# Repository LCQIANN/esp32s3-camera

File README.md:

# ESP32-S3 Camera — v1.4

以 ESP32-S3-WROOM-1-N16R8 為核心的隨身相機板：OV2640 DVP 相機、microSD 存檔、USB-C 燒錄與充電、鋰電池供電、電源開關與電源燈，1.3 吋 ST7789 預覽螢幕直接插在背面的母座上，快門在上板邊側按。v1.3 起為 3D 列印相機式外殼（鏡頭正面、螢幕背面）而改，v1.4 把快門移到上板邊。KiCad 10 專案，設計成直接送 JLCPCB PCBA。

| 項目 | 規格 |
|---|---|
| 板子 | 60 × 85 mm、4 層（In1 = GND、In2 = +3V3）、1.6 mm、四角 M2 孔 |
| 主控 | U1 ESP32-S3-WROOM-1-N16R8（16 MB flash、8 MB OPI PSRAM） |
| 相機 | J2 24P 0.5 mm FPC 座，AI-Thinker ESP32-CAM 標準腳位；U5 2.8V、U6 1.2V LDO 供相機 |
| 儲存 | J3 microSD（SDMMC），開口朝左板邊 |
| 電源 | J1 USB-C → U3 TP4056 充電 → J4 JST PH 2.0 鋰電池；U2 AP2112K 3.3V LDO；SW4 滑動開關控制 LDO EN；D5 藍色電源燈 |
| 操作 | SW3 SHUTTER 側按式（ALPS SKRTLAE010）在上板邊右段 (50.6, 2.6)；SW1 BOOT、SW2 RESET 頂面按壓式在左欄；D1 綠、D2 紅（充電）、D4 白 LED |
| 螢幕 | J5 1×7 2.54 mm 母座（底面右板邊），通用型 1.3 吋 IPS 240×240 ST7789 7 pin 模組，用七條公–母杜邦線接（2026-09-23 起；也可直插）；SCL=GPIO44、SDA=GPIO43、RES=GPIO6、DC=GPIO5、BLK=GPIO4。UART0 排針已取消 |
| 零件 | 60 顆：58 SMD 由 JLCPCB 貼片，2 插件（J4 電池座、J5 螢幕母座） |
| 狀態 | v1.4，2026-09-22 定稿。ERC 0、DRC 0/0/0、原理圖一致性 0、GND/3V3 連通性 0 孤立焊盤 |

## 目前狀態

- **v1.4 已定稿，可下單。** 快照在 `versions/v1.4/`，含 Gerber、BOM、CPL、ERC/DRC 報告，視為唯讀。v1.2、v1.3 都沒有下單。
- **預覽螢幕用七條公–母杜邦線接板上母座 J5**（2026-09-23 決定，省事不焊；腳序一對一）。模組鎖在後殼四支矮柱上、蓋在電池上方，亮面離板底約 26.4 mm；外殼後半因為杜邦膠殼加深到 27 mm 內深，整機 40.1 mm。細節與外殼用的尺寸在 `DESIGN.md` 2d 節與 `enclosure/README.md`。
- 版本沿革：v1.0 最初佈局 → v1.1 相機腳位改 ESP32-CAM 標準、加相機 LDO、填 LCSC 料號 → v1.2 加 SW4、R21、R20、D5 與 ON/OFF 絲印 → v1.3 J5/J6 兩條排針換成 1×7 螢幕母座 J5（SMD 與 CPL 不變）→ v1.4 快門 SW3 換成側按式移到上板邊右段，C12 下移 0.8 mm（CPL 只差這兩行）。
- 外殼相關但仍刻意沒改：LED 分兩面、板邊開口分三邊（USB-C 與開關右邊、記憶卡左邊、快門上邊）。
- 送洗前檢查補了兩顆 GND 過孔（J2.23、C3.2 原本焊盤浮接），細節見 `DESIGN.md` 第 3 節。

## 簡報

| 檔案 | 給誰看 | 內容 |
|---|---|---|
| `esp32s3-camera-v1.4-簡易版.pptx` / `.pdf` | 外行人、家人朋友、沒碰過電路板的人 | 11 頁，不用零件編號與專業縮寫：它能做什麼、正反面長什麼樣、工廠做哪些我們做哪些、要買什麼、三步組裝、三件注意事項、外殼長這樣、裝進殼裡長這樣 |
| `esp32s3-camera-v1.4.pptx` / `.pdf` | 自己下單與組裝時對照、有電子背景的人 | 21 頁完整版：依 PCB 座標畫的零件分工圖、Economic / Standard 差異、58 顆 SMD 清單、3D 渲染、組裝尺寸與高度、四頁 3D 列印外殼（含板外零件裝配檢查與杜邦線走線）、含購買連結的採購表；2026-09-23 已更新為杜邦線版 |

另有一個線上頁面「ESP32-S3 相機板零件分工圖」（claude.ai 私人連結，組織內可看），2026-09-23 已更新到 v1.4 杜邦線版：依座標畫的零件分工圖、組裝示意與裸板 3D 渲染、外殼與杜邦線走線渲染、採購清單。

兩份都用 PowerPoint 匯出成 PDF，PDF 內的購買連結可點。兩份簡報 2026-09-23 已更新到 v1.4（螢幕母座、側按快門、外殼）；更新方式是 `tools/update_decks_v14.py` 在 v1.2 檔上改文字、換圖、加頁，再用 `tools/export_decks.py` 叫 PowerPoint 匯出 PDF 與檢查用的 PNG。

## 檔案地圖

```
esp32s3-camera/
├── README.md                     本檔
├── DESIGN.md                     設計規格書：決策、腳位、電路細節、組裝與機構、版本規則
├── esp32s3-camera.kicad_pro/.kicad_sch/.kicad_pcb   KiCad 10 專案（根目錄永遠是最新版）
├── esp32s3-camera.pretty/        自訂 footprint（ESP32-S3-WROOM-1-Cam）
├── esp32s3-camera.step           板子 STEP，給外殼設計用
├── erc.rpt / drc.rpt / netlist.net
├── view-top.png / view-bottom.png   v1.4 頂面、底面 3D 正視
├── esp32s3-camera-v1.4.pptx / .pdf   零件分工、組裝示意、渲染圖、外殼、採購清單簡報（完整版 20 頁）
├── esp32s3-camera-v1.4-簡易版.pptx / .pdf   給外行人看的 11 頁簡易版
├── tools/                        簡報更新與匯出腳本（python-pptx + PowerPoint COM）
│
├── fab/                          送廠檔案
│   ├── esp32s3-camera-gerber.zip   Gerber + 鑽孔打包
│   ├── esp32s3-camera-bom.csv      BOM，含 LCSC Part # 欄
│   ├── esp32s3-camera-cpl.csv      貼片座標
│   ├── gerber/                     未打包的 Gerber、鑽孔檔
│   ├── JLCPCB-上傳-v1.4/            上傳用三個檔案的重新命名版 + 一頁說明
│   ├── JLCPCB-下單清單.md           下單逐步核對表，含收到板子後的第一次上電
│   └── 採購清單.md                  板外零件與插件的購買網址
│
├── render/                       kicad-cli 光線追蹤渲染
│   ├── iso-*/top/bottom/low-angle/closeup-*.png   裸板貼片後
│   ├── assembled-*.png / closeup-camera-module.png   插相機、記憶卡、電池、螢幕的組裝示意
│   └── illustration/             示意渲染專用的板檔複本、簡化 VRML 模型、輔助腳本（見下）
│
├── versions/                     各版完整快照，唯讀
│   ├── v1.0/  v1.1/  v1.2/  v1.3/  v1.4/   每版有 README.txt 說明改了什麼
│
├── enclosure/                    3D 列印外殼：SolidWorks 前殼、後殼、按鈕帽、組合件、STL、渲染圖與產生腳本（見 enclosure/README.md）
├── firmware/                     Arduino 韌體：預覽、拍照存卡、閃光燈（見 firmware/README.md）
├── frames/                       2026-09-11 早期佈局的旋轉截圖，僅供回顧
└── .history/                     KiCad 自動快照，由 KiCad 管理
```

`render/illustration/esp32s3-camera-illustration.kicad_pcb` 多了三個沒有焊盤的假零件掛簡化模型，**只用來渲染，不要拿它出 Gerber**。

## 怎麼下單

1. 依 `fab/JLCPCB-下單清單.md` 逐項核對。上傳 `fab/esp32s3-camera-gerber.zip`、`esp32s3-camera-bom.csv`、`esp32s3-camera-cpl.csv`。
2. PCB：4 層、60 × 85 mm、1.6 mm、1 oz、ENIG 建議、Tented via，最少 5 片。
3. PCBA：雙面貼片，最少 2 片。
   - **Economic** 只焊 SMD：J4 電池座、J5 1×7 母座（C225482）自己買回來手焊。
   - **Standard** 含插件：兩顆一起焊好。
4. 料號配對頁逐行看：U1 `C2913202`（N16R8，可能預購，不要被換成 N8 或無 R 版）、D3 `C8598`（SOD-123，不是 SS14）、SW4 `C431540`、SW3 `C110293`（ALPS SKRTLAE010 側按，不要被換成頂按式）。
5. 零件擺放預覽確認方向：U1 天線端朝板子底邊、J1 開口朝板邊、J2 掀蓋朝板邊、SW4 撥桿朝右板邊、**SW3 觸桿朝上板邊**、J5 母座在底面、方形 pin 1 焊盤朝天線那一端。

## 板外要自己買的

相機模組、鋰電池、microSD 卡、USB-C 線是最小採購；Economic 方案再加 J4 電池座。完整清單與購買網址在 `fab/採購清單.md`。

| 品項 | 規格 | 接到 |
|---|---|---|
| OV2640 相機模組 | 24 pin 0.5 mm 排線，ESP32-CAM 相容，排線約 21 mm，多買一條備用 | J2 |
| 3.7V 鋰電池 | 603040 或 503040 約 600 mAh，帶保護板，JST PH 2.0 插頭 | J4 |
| microSD 卡 | 8–32 GB | J3 |
| USB-C 線 | 要能傳資料 | J1 |
| 預覽螢幕 | 通用型 1.3 吋 IPS 240×240 ST7789，7 pin 2.54 mm 直排針已焊，27.78 × 39.22 mm | 七條公–母杜邦線接 J5 |
| 杜邦線 | 公–母、10 cm、7 條 | 公頭插 J5、母頭套螢幕排針 |
| M2 螺絲與銅柱 | 板子 4 組 | H1–H4 |
| 雙面泡棉膠 | 約 2 mm 厚 | 相機模組與電池底下 |

## 組裝重點

- **相機**：排線接觸面朝下插入 J2，出來約 2.5 mm 就反折 180° 蓋回 J2，模組貼在按鍵欄與 U4 之間的空區（x 25.5–34.5、y 20.5–29.5 mm），鏡頭中心 (30, 25)，底下墊 8 × 8 mm 泡棉膠。
- **電池**：貼在底面中央 (34, 44)，墊 2 mm 泡棉，保護板端朝下緣。**J4 pin 1 = 正極**，在 L 形絲印那一側、靠板子中央。電池插頭極性沒有統一規範，插之前先量。
- **螢幕**：模組排針對準底面右板邊的 J5 母座直接插到底，亮面朝外、身體蓋在電池上方。腳序一對一：GND、3V3、SCL (GPIO44)、SDA (GPIO43)、RES (GPIO6)、DC (GPIO5)、BLK (GPIO4)，板上每格都有絲印，**第一次插之前先對一下模組上的 GND 字有沒有對到板上 GND 那格**。借用 UART0 腳位當 SPI，USB 序列埠仍可用。
- **快門**：SW3 在上板邊右段，觸桿朝板邊伸出 0.56 mm 內，由外殼上牆的快門帽按壓；不裝外殼時用指甲從板邊按。BOOT、RESET 仍在鏡頭面左欄。
- **電源開關**：撥向板子上緣（角落孔那側）= OFF，撥向模組 = ON，絲印已標。關機時 USB 仍可充電，D2 紅燈照常。D5 藍燈接 3.3V，開機必亮。
- **microSD**：從左板邊插入 J3，金手指朝電路板，推到「喀」一聲。
- **底面高度**：電池 + 泡棉 8 mm；J5 上的杜邦公頭膠殼到板底下 22.5 mm；螢幕模組背面離板底 23.6 mm、亮面 26.4 mm，外殼底側內深 27.0 mm。
- **外殼開孔**：鏡頭 (30, 25) 頂面；快門上板邊 x 47.6–53.6、板頂以上 0.2–4.4 mm；BOOT/RESET 針孔 (9, 24)、(9, 32)；開關右板邊 y 8–14；USB-C 右板邊 y 19.5–28.5；記憶卡左板邊 y 36–52；螢幕窗 23.4 × 23.4 mm，中心約 (28.4, 45) 底面。板子 STEP 在 `esp32s3-camera.step`，含母座；螢幕模組的簡化模型在 `render/illustration/models/display_module.wrl`。

## 外殼

`enclosure/` 是給 v1.4 板子的相機式兩片殼（前殼鏡頭面、後殼螢幕面，快門帽在上牆），用 `enclosure/build_enclosure_sw.py` 透過 SolidWorks 2024 的 API 依板檔座標自動建模，組合件含板子 STEP 與板外零件簡化模型，干涉檢查 0 件。螢幕模組用四支 M2×4 鎖在後殼的矮柱上、以七條杜邦線接 J5，快門帽在上牆。外形 65 × 90 × 40.1 mm，四支 M2×35 從背面鎖。組合件連相機模組、排線反折、電池與電池線、記憶卡、螢幕模組、杜邦線的簡化模型都放進去做過干涉檢查，0 件。尺寸依據、列印方向、組裝步驗與第一次實體要驗證的項目都在 `enclosure/README.md`。

## 收到板子後的第一次上電

先不插相機與電池。接 USB-C 撥 SW4 看 D5 亮滅，量 +3V3 / +2V8 / +1V2 對地無短路且電壓正確，電腦看到 ESP32-S3 USB 裝置，燒 blink 測 D1。都過了再依序插 microSD、相機排線、最後接電池。完整清單在 `fab/JLCPCB-下單清單.md` 第 8 節。

## 韌體

`firmware/esp32s3-camera/` 是 Arduino 專案（2026-10-10 起）：OV2640 即時預覽顯示在 ST7789 上，側邊快門拍 1600 × 1200 JPEG 存到 microSD `/DCIM/`，BOOT 鍵切換閃光燈。腳位全在 `firmware/esp32s3-camera/board_pins.h`，與 `DESIGN.md` 第 4 節一致。Board 選 **ESP32S3 Dev Module**，PSRAM 選 **OPI PSRAM**（R8 是 octal，選 QSPI 會抓不到），Flash 16MB，USB CDC On Boot 開。編譯設定、arduino-cli 指令、尚未在硬體驗證的項目見 `firmware/README.md`。板子還沒下單，韌體目前只確認能編譯（核心 3.3.10）。

## 版本規則

- 根目錄永遠是正在改的最新版。每次出 Gerber 準備下單，把 `.kicad_pcb / .kicad_sch / .kicad_pro`、`esp32s3-camera.pretty/`、`fp-lib-table` 與 `fab/` 內的 zip、BOM、CPL 複製到 `versions/vX.Y/`，並寫 README.txt。
- 版本號用數字（v1.0、v1.1、v1.2），不用 rev A / rev B。板上絲印、KiCad 標題欄、Gerber ProjectId 三處同步。
- 不在根目錄留 `*.bak_before_xxx`，中途快照交給 KiCad 的 `.history/`。
- 2026-09-21 起以 Git 管理，遠端為公開的 GitHub LCQIANN/esp32s3-camera；`versions/` 的快照仍照上面規則保留。

## 重新輸出送廠檔

```
kicad-cli sch export bom --fields "Reference,Value,Footprint,QUANTITY,LCSC" --labels "Designator,Comment,Footprint,Qty,LCSC Part #" --group-by "Value,Footprint,LCSC" --exclude-dnp -o fab/esp32s3-camera-bom.csv esp32s3-camera.kicad_sch
kicad-cli pcb drc --schematic-parity esp32s3-camera.kicad_pcb
```

## 輔助腳本（`render/illustration/`，用 KiCad 附的 python 執行）

| 腳本 | 用途 |
|---|---|
| `gnd_connectivity.py` | 幾何連通性檢查：焊盤、過孔、走線、敷銅做 union-find，確認每個 GND / +3V3 焊盤都在主群集。**DRC 只要有 unconnected_items 就跑一次，0 才算過。** |
| `battery_check.py` | 電池投影範圍對底面零件外框與高度的間距核對 |
| `fix_v12_gnd.py` | 2026-09-21 補 J2.23、C3.2 GND 過孔與 R21 腳位修正 |
| `v12_sch.py` / `v12_pcb.py` / `v12_silk_onoff.py` | v1.2 加 SW4、R20、R21、D5 與 ON/OFF 絲印的自動改板腳本 |
| `make_illustration_board.py` | 產生示意渲染用的板檔複本 |
| `gen_camera_wrl.py` / `gen_display_wrl.py` | 產生相機模組與螢幕的簡化 VRML 模型（KiCad 不畫 Cylinder 基本體，圓柱要用網格） |
| `sch_inspect.py` | 原理圖檢查工具 |

## 教訓

- DRC 報的「zone unconnected」不要當敷銅碎片忽略。KiCad 只回報兩群集間最近的一對物件，浮接的焊盤會藏在後面。
- D3 要用 B5819W SOD-123（`C8598`），LCSC 上的 SS14 是 SMA 封裝，焊盤不合。
- JLCPCB 的零件旋轉定義與 KiCad 不一定一致，零件擺放預覽頁逐一看有極性的零件。

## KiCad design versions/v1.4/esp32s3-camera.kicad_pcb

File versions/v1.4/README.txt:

v1.4 — 2026-09-22 定稿（v1.3 未下單，直接改成 v1.4）。
起因：三顆按鍵都在鏡頭面左欄，拿相機時要繞到前面盲按，不符合人體工學。
相對 v1.3 的改動：快門 SW3 從頂面按壓式 SKQG (9, 40) 換成側按式 ALPS SKRTLAE010（LCSC C110293），
放在上板邊右段 (50.6, 2.6) 轉 180 度，觸桿朝板邊伸出，桿頭在 y = 0.56，由外殼上牆的快門帽按壓。
封裝用專案內複本 esp32s3-camera:SW_Push_SKRTLAE010_Side（焊盤 1 由 0.75 縮到 0.55 mm，與定位孔留 0.15 mm）。
C12 下移 0.8 mm 到 (47.5, 6.3) 讓位；刪掉 GND 縫合過孔 (51,3)、(54,3)、(22.4,73.8)、(40,73.8)；IPROG 頂層斜線改繞 GND 過孔 (45.7,7.3)。
BTN_SHUTTER 走線：U1 pin 39 (21.25,72.49) 往左打過孔 (19.4,73.4)，底層沿模組下方 y = 73.3..73.4 到右板邊，沿 x = 59.35 往上到 y = 2，過孔 (53.8,2) 回頂層接 SW3；
原本到左欄 SW3 的 16 段頂層走線刪除。SW1 BOOT、SW2 RESET 不動。
58 顆 SMD 不變（SW3 換料號），CPL 只有 C12 與 SW3 兩行不同；插件 J4、J5。零件 60 顆。絲印、標題欄、Gerber ProjectId 皆為 v1.4。
驗證：ERC 0 錯誤（2 個 XC6206 符號庫警告）；DRC 含原理圖一致性 0 錯誤、0 警告、0 未連接、0 一致性問題；gnd_connectivity.py GND / +3V3 全部焊盤在主群集。
內容：原理圖、板檔、專案檔、網表、ERC/DRC 報告、fab/（Gerber zip、鑽孔、BOM 34 行、CPL 58 顆、JLCPCB-上傳-v1.4、下單清單、採購清單）、自訂 footprint 庫。
外殼：enclosure/ 同步改為 v1.4（快門帽在上牆、BOOT/RESET 針孔），組合件干涉 0 件。
腳本：render/illustration/v14_sch.py、v14_pcb.py、v14_pcb_fix.py、v14_pcb_fix2.py。
此資料夾視為唯讀。

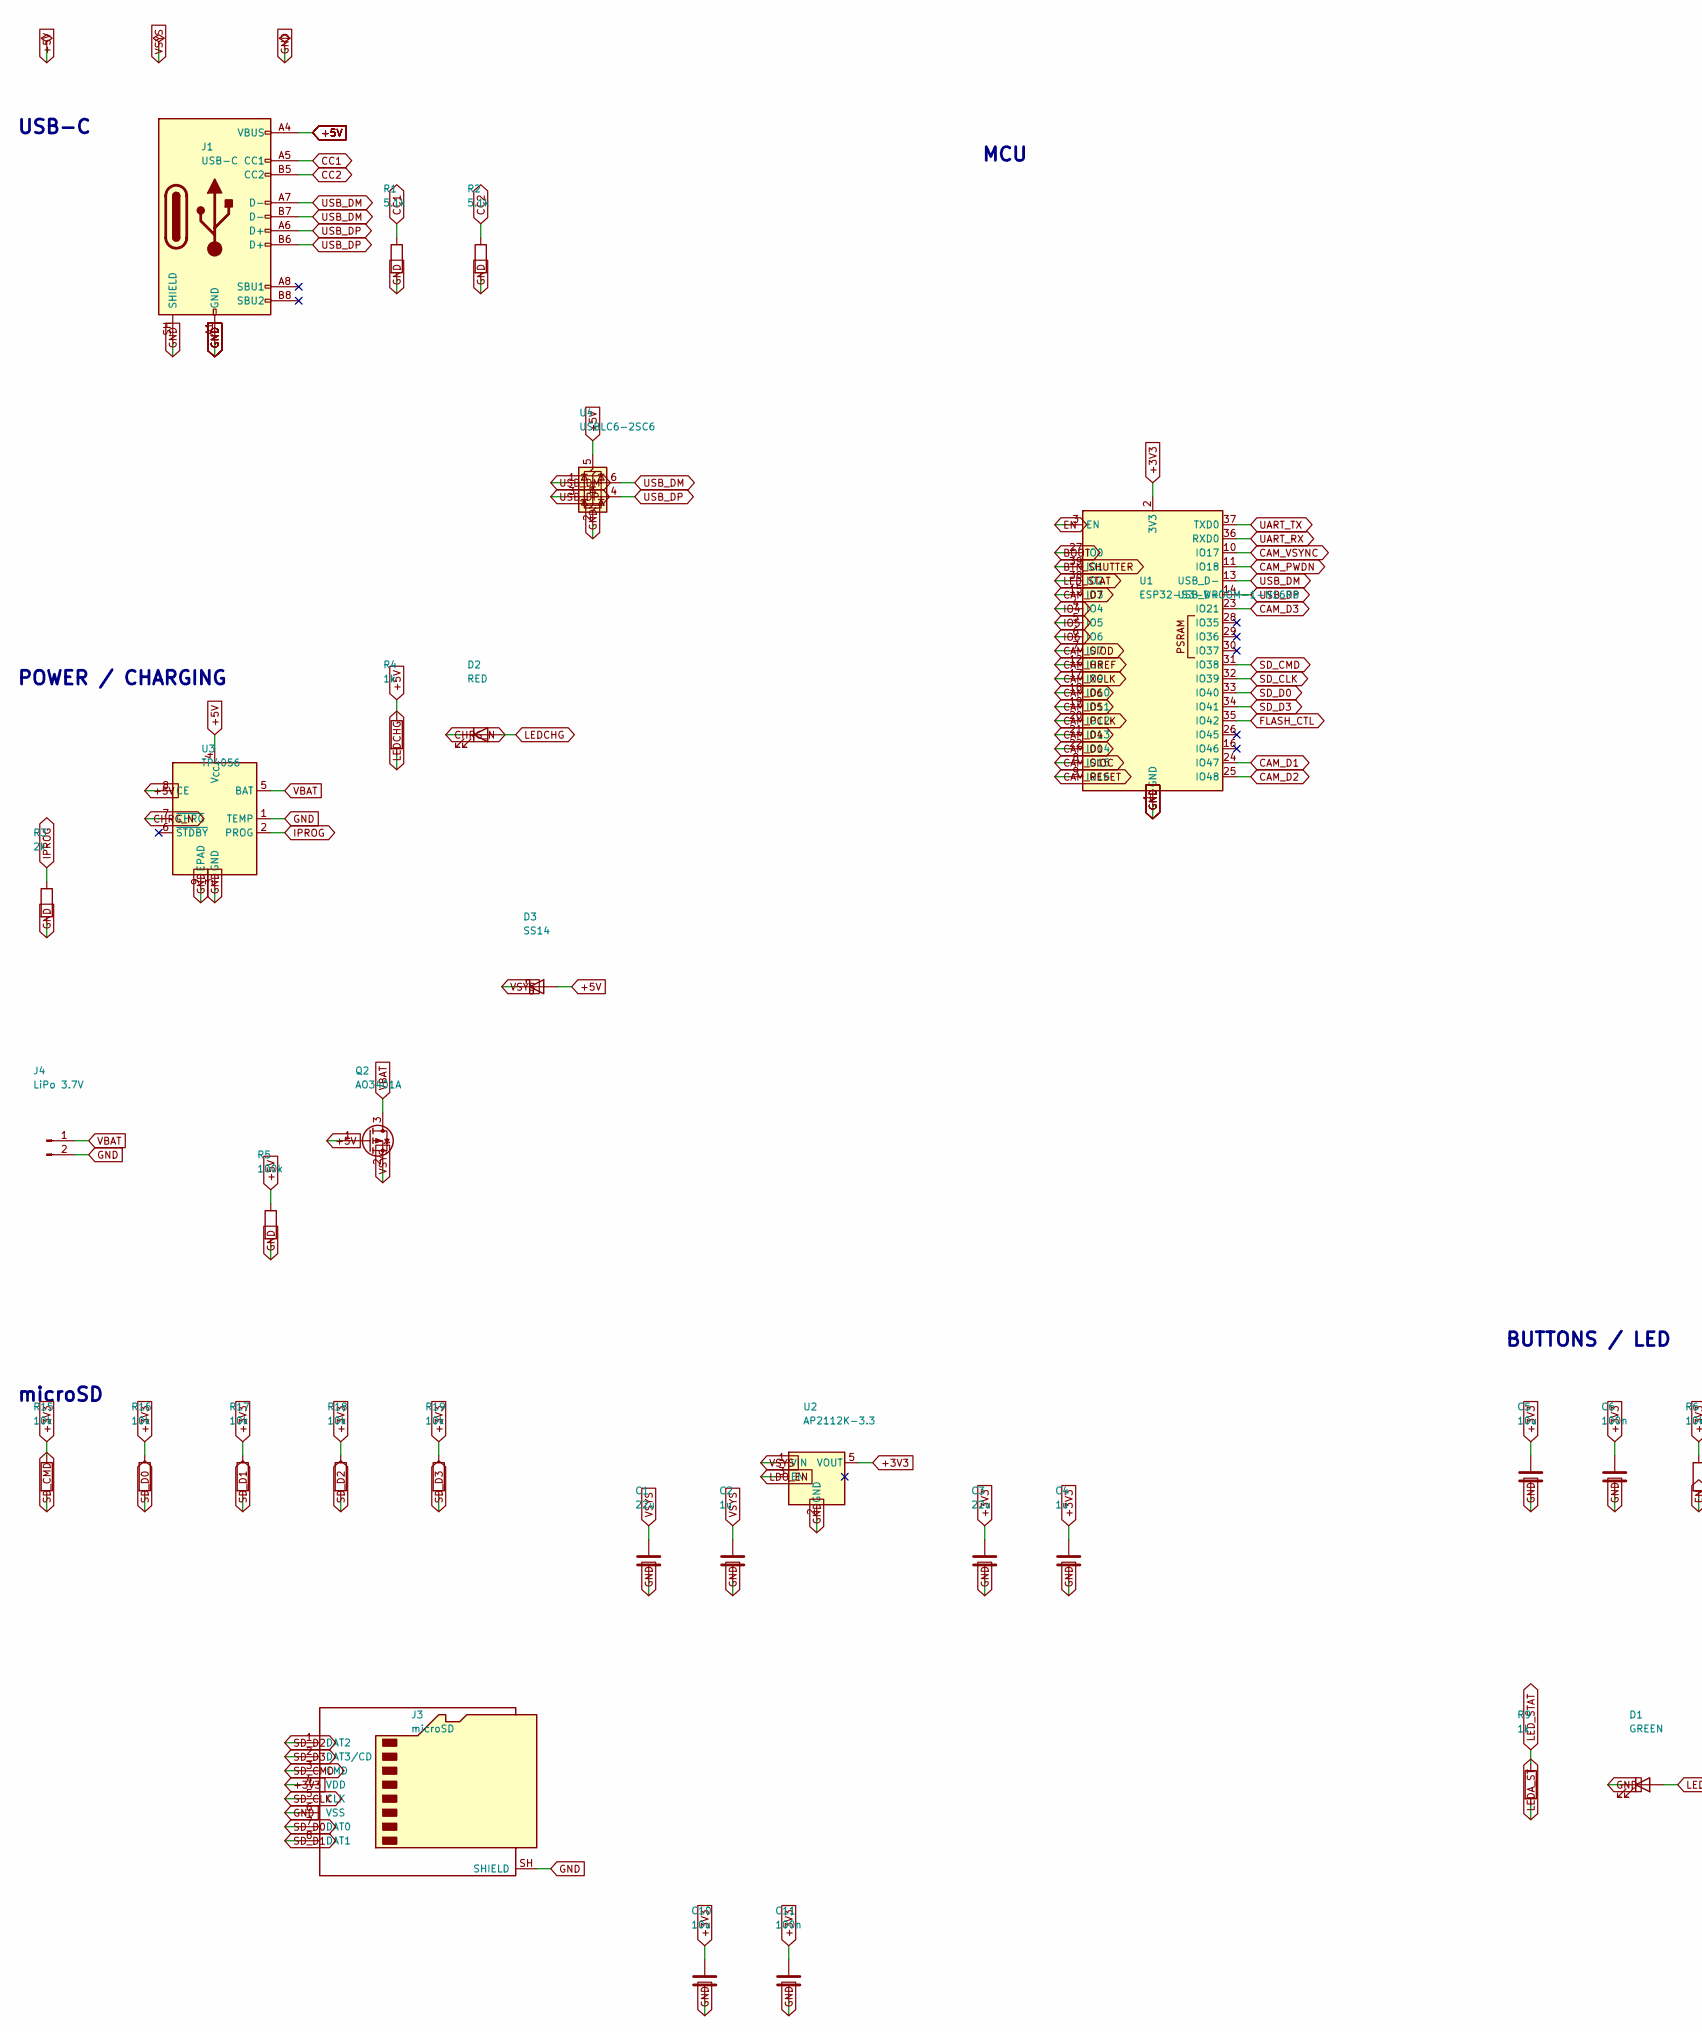
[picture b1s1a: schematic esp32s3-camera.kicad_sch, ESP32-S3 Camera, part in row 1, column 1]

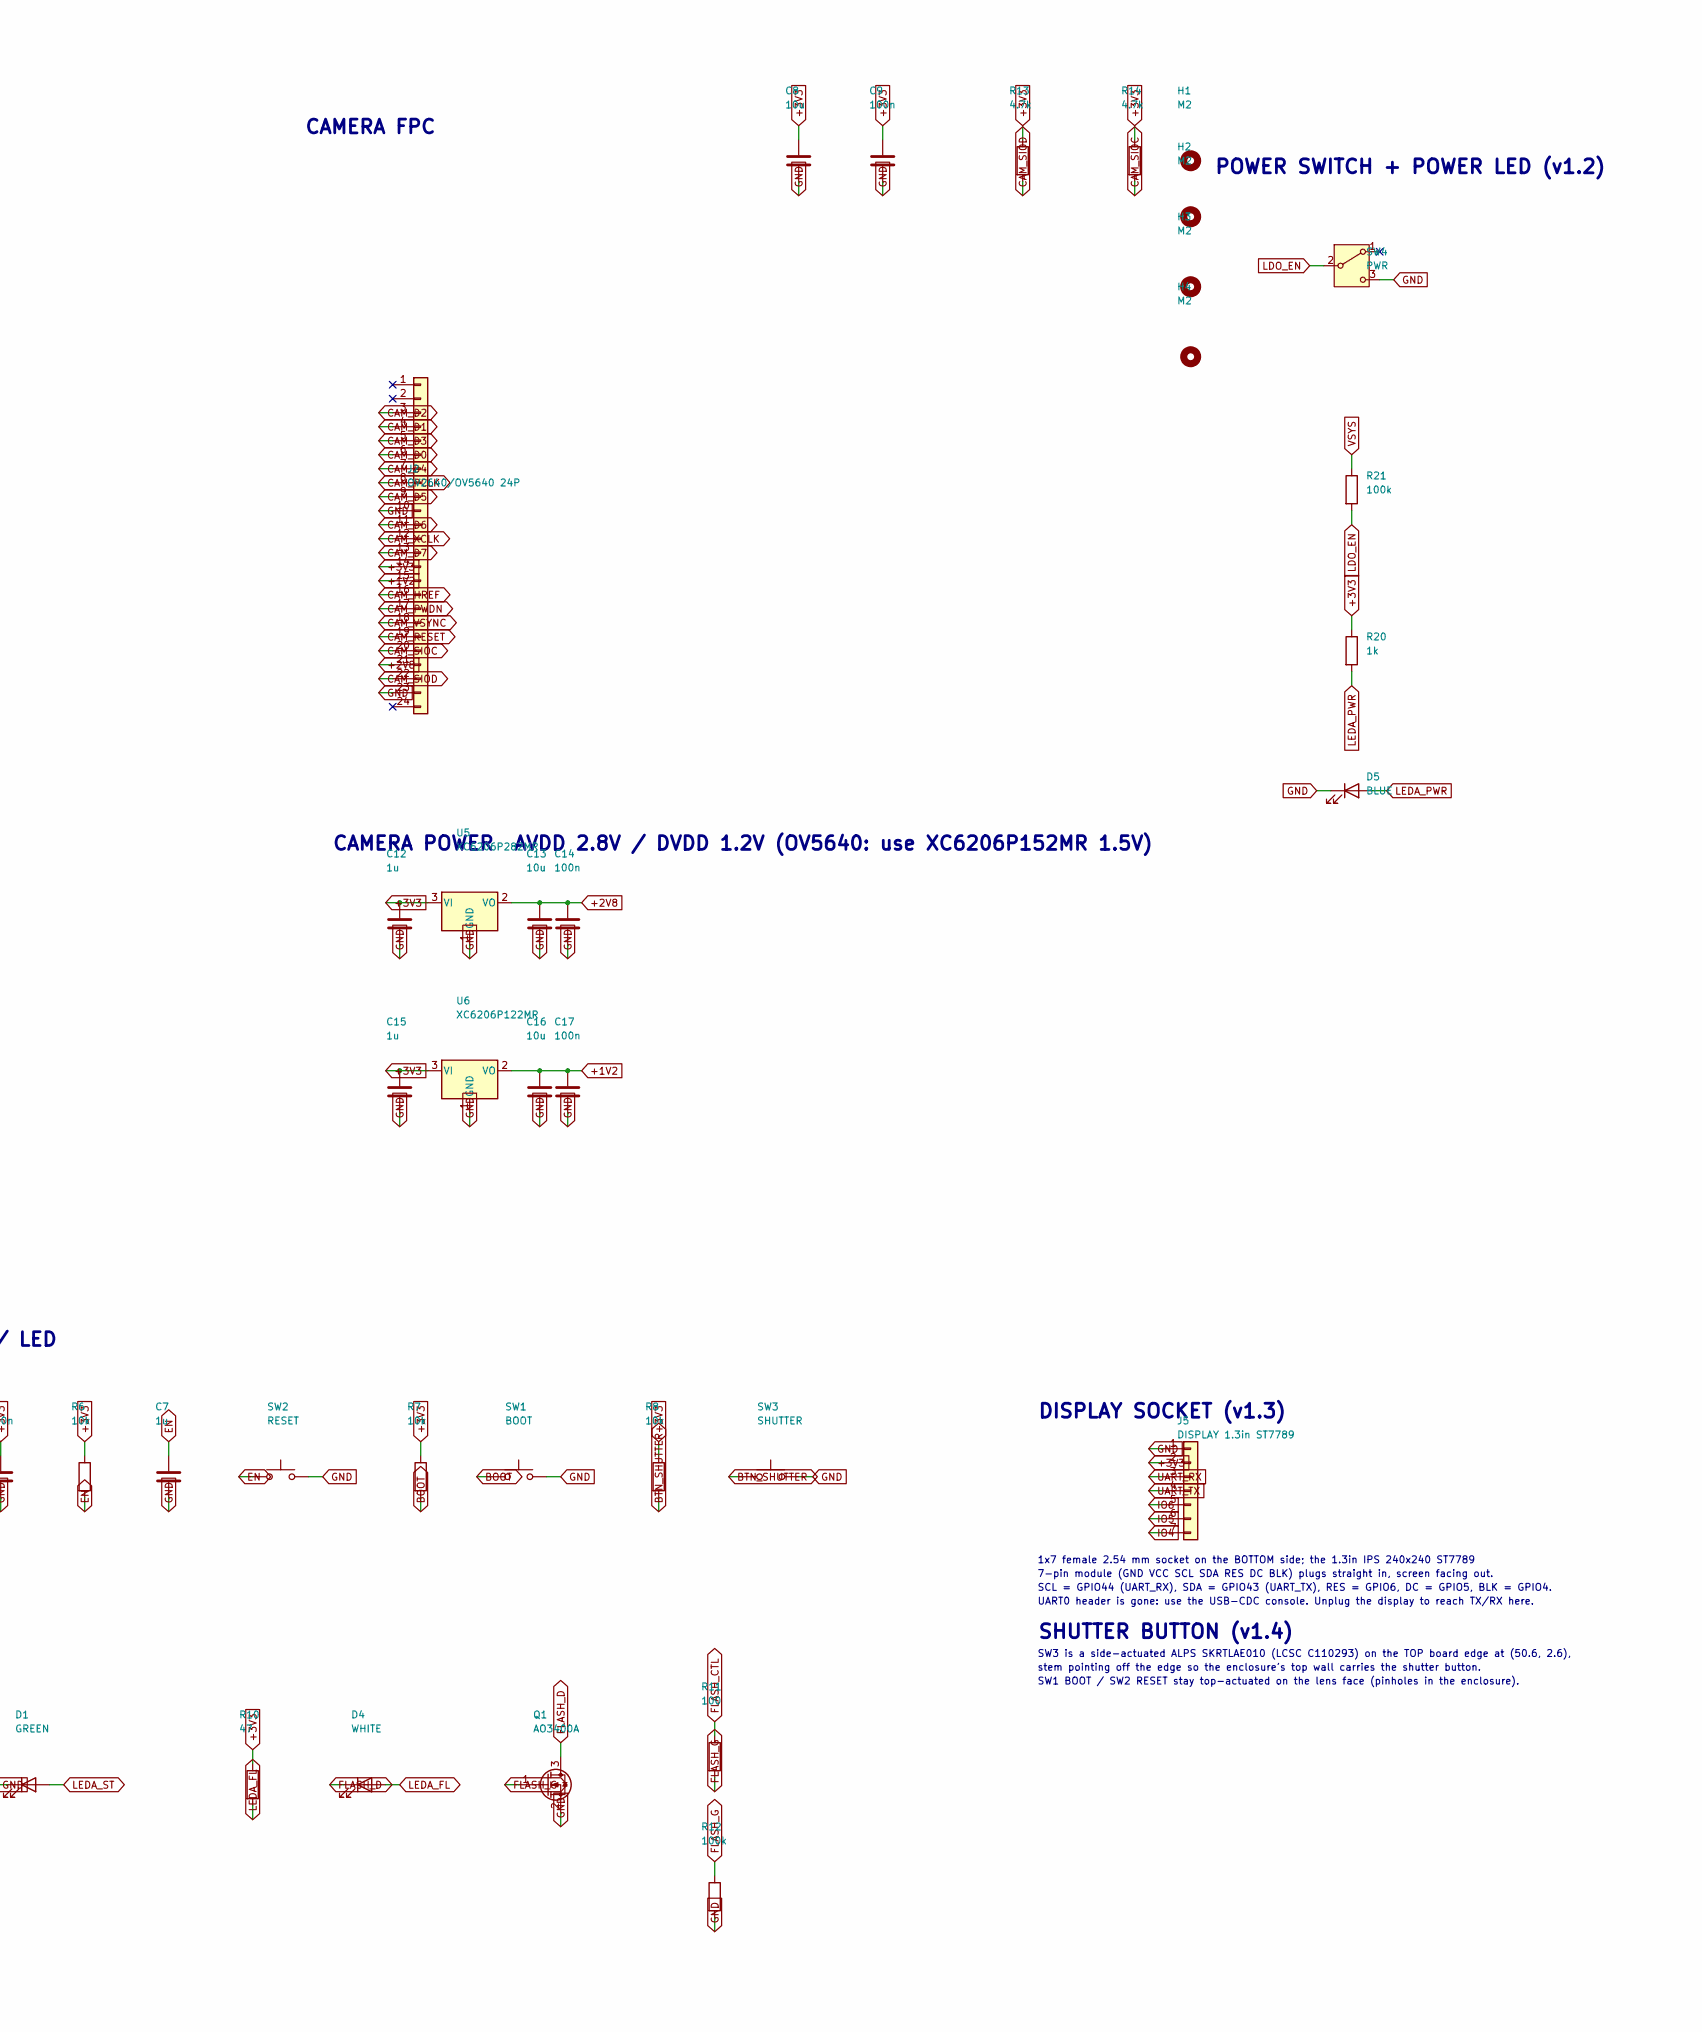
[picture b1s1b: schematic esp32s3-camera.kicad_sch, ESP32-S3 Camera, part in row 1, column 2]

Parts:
C1, C3: 22u; C_0805_2012Metric; LCSC C45783
C2, C4, C7, C12, C15: 1u; C_0603_1608Metric; LCSC C15849
C5, C8, C10, C13, C16: 10u; C_0805_2012Metric; LCSC C15850
C6, C9, C11, C14, C17: 100n; C_0603_1608Metric; LCSC C14663
D1: GREEN; LED_0603_1608Metric; LCSC C72043
D2: RED; LED_0603_1608Metric; LCSC C2286
D3: SS14; D_SOD-123; LCSC C8598
D4: WHITE; LED_0603_1608Metric; LCSC C2290
D5: BLUE; LED_0603_1608Metric; LCSC C2288
H1, H2, H3, H4: M2; MountingHole_2.2mm_M2
J1: USB-C; USB_C_Receptacle_HCTL_HC-TYPE-C-16P-01A; LCSC C2894897
J2: OV2640/OV5640 24P; Hirose_FH12-24S-0.5SH_1x24-1MP_P0.50mm_Horizontal; LCSC C202112
J3: microSD; microSD_HC_Hirose_DM3AT-SF-PEJM5; LCSC C114218
J4: LiPo 3.7V; JST_PH_B2B-PH-K_1x02_P2.00mm_Vertical; LCSC C131337
J5: DISPLAY 1.3in ST7789; PinSocket_1x07_P2.54mm_Vertical; LCSC C225482
Q1: AO3400A; SOT-23; LCSC C20917
Q2: AO3401A; SOT-23; LCSC C15127
R1, R2: 5.1k; R_0603_1608Metric; LCSC C23186
R3: 2k; R_0603_1608Metric; LCSC C22975
R4, R9, R20: 1k; R_0603_1608Metric; LCSC C21190
R5, R12, R21: 100k; R_0603_1608Metric; LCSC C25803
R6, R7, R8, R15, R16, R17, R18, R19: 10k; R_0603_1608Metric; LCSC C25804
R10: 47; R_0603_1608Metric; LCSC C23182
R11: 100; R_0603_1608Metric; LCSC C22775
R13, R14: 4.7k; R_0603_1608Metric; LCSC C23162
SW1: BOOT; SW_SPST_SKQG_WithoutStem; LCSC C115351
SW2: RESET; SW_SPST_SKQG_WithoutStem; LCSC C115351
SW3: SHUTTER; SW_Push_SKRTLAE010_Side; LCSC C110293
SW4: PWR; SW_SPDT_Shouhan_MSK12C02; LCSC C431540
U1: ESP32-S3-WROOM-1-N16R8; ESP32-S3-WROOM-1-Cam; LCSC C2913202
U2: AP2112K-3.3; SOT-23-5; LCSC C51118
U3: TP4056; SOIC-8-1EP_3.9x4.9mm_P1.27mm_EP2.41x3.3mm; LCSC C16581
U4: USBLC6-2SC6; SOT-23-6; LCSC C7519
U5: XC6206P282MR; SOT-23-3; LCSC C14255
U6: XC6206P122MR; SOT-23-3; LCSC C424699

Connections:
+1V2: C16.1, C17.1, J2.15, U6.2 (VO)
+2V8: C13.1, C14.1, J2.21, U5.2 (VO)
+3V3: C3.1, C4.1, C5.1, C6.1, C8.1, C9.1, C10.1, C11.1, C12.1, C15.1, J2.14, J3.4 (VDD), J5.2, R6.1, R7.1, R8.1, R10.1, R13.1, R14.1, R15.1, R16.1, R17.1, R18.1, R19.1, R20.1, U1.2 (3V3), U2.5 (VOUT), U5.3 (VI), U6.3 (VI)
+5V: D3.2 (A), J1.A4 (VBUS), J1.A9 (VBUS), J1.B4 (VBUS), J1.B9 (VBUS), Q2.1 (G), R4.1, R5.1, U3.4 (V_{CC}), U3.8 (CE), U4.5 (VBUS)
BOOT: R7.2, SW1.1, U1.27 (IO0)
BTN_SHUTTER: R8.2, SW3.1, U1.39 (IO1)
CAM_D0: J2.6, U1.22 (IO14)
CAM_D1: J2.4, U1.24 (IO47)
CAM_D2: J2.3, U1.25 (IO48)
CAM_D3: J2.5, U1.23 (IO21)
CAM_D4: J2.7, U1.21 (IO13)
CAM_D5: J2.9, U1.19 (IO11)
CAM_D6: J2.11, U1.18 (IO10)
CAM_D7: J2.13, U1.15 (IO3)
CAM_HREF: J2.16, U1.12 (IO8)
CAM_PCLK: J2.8, U1.20 (IO12)
CAM_PWDN: J2.17, U1.11 (IO18)
CAM_RESET: J2.19, U1.9 (IO16)
CAM_SIOC: J2.20, R14.2, U1.8 (IO15)
CAM_SIOD: J2.22, R13.2, U1.7 (IO7)
CAM_VSYNC: J2.18, U1.10 (IO17)
CAM_XCLK: J2.12, U1.17 (IO9)
CC1: J1.A5 (CC1), R1.1
CC2: J1.B5 (CC2), R2.1
CHRG_N: D2.1 (K), U3.7 (~CHRG)
EN: C7.1, R6.2, SW2.1, U1.3 (EN)
FLASH_CTL: R11.1, U1.35 (IO42)
FLASH_D: D4.1 (K), Q1.3 (D)
FLASH_G: Q1.1 (G), R11.2, R12.1
GND: C1.2, C2.2, C3.2, C4.2, C5.2, C6.2, C7.2, C8.2, C9.2, C10.2, C11.2, C12.2, C13.2, C14.2, C15.2, C16.2, C17.2, D1.1 (K), D5.1 (K), J1.A1 (GND), J1.A12 (GND), J1.B1 (GND), J1.B12 (GND), J1.SH (SHIELD), J2.10, J2.23, J3.6 (VSS), J3.SH (SHIELD), J4.2, J5.1, Q1.2 (S), R1.2, R2.2, R3.2, R5.2, R12.2, SW1.2, SW2.2, SW3.2, SW4.3 (C), U1.1 (GND), U1.40 (GND), U1.41 (GND), U2.2 (GND), U3.1 (TEMP), U3.3 (GND), U3.9 (EPAD), U4.2 (GND), U5.1 (GND), U6.1 (GND)
IO4: J5.7, U1.4 (IO4)
IO5: J5.6, U1.5 (IO5)
IO6: J5.5, U1.6 (IO6)
IPROG: R3.1, U3.2 (PROG)
LDO_EN: R21.2, SW4.2 (B), U2.3 (EN)
LEDA_FL: D4.2 (A), R10.2
LEDA_PWR: D5.2 (A), R20.2
LEDA_ST: D1.2 (A), R9.2
LEDCHG: D2.2 (A), R4.2
LED_STAT: R9.1, U1.38 (IO2)
SD_CLK: J3.5 (CLK), U1.32 (IO39)
SD_CMD: J3.3 (CMD), R15.2, U1.31 (IO38)
SD_D0: J3.7 (DAT0), R16.2, U1.33 (IO40)
SD_D1: J3.8 (DAT1), R17.2
SD_D2: J3.1 (DAT2), R18.2
SD_D3: J3.2 (DAT3/CD), R19.2, U1.34 (IO41)
UART_RX: J5.3, U1.36 (RXD0)
UART_TX: J5.4, U1.37 (TXD0)
USB_DM: J1.A7 (D-), J1.B7 (D-), U1.13 (USB_D-), U4.1 (I/O1), U4.6 (I/O1)
USB_DP: J1.A6 (D+), J1.B6 (D+), U1.14 (USB_D+), U4.3 (I/O2), U4.4 (I/O2)
VBAT: J4.1, Q2.3 (D), U3.5 (BAT)
VSYS: C1.1, C2.1, D3.1 (K), Q2.2 (S), R21.1, U2.1 (VIN)

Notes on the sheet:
BUTTONS / LED
POWER / CHARGING
MCU
microSD
CAMERA FPC
USB-C
CAMERA POWER AVDD 2.8V / DVDD 1.2V (OV5640: use XC6206P152MR 1.5V)
POWER SWITCH + POWER LED (v1.2)
DISPLAY SOCKET (v1.3)
1x7 female 2.54 mm socket on the BOTTOM side; the 1.3in IPS 240x240 ST7789
7-pin module (GND VCC SCL SDA RES DC BLK) plugs straight in, screen facing out.
SCL = GPIO44 (UART_RX), SDA = GPIO43 (UART_TX), RES = GPIO6, DC = GPIO5, BLK = GPIO4.
UART0 header is gone: use the USB-CDC console. Unplug the display to reach TX/RX here.
SHUTTER BUTTON (v1.4)
SW3 is a side-actuated ALPS SKRTLAE010 (LCSC C110293) on the TOP board edge at (50.6, 2.6),
stem pointing off the edge so the enclosure's top wall carries the shutter button.
SW1 BOOT / SW2 RESET stay top-actuated on the lens face (pinholes in the enclosure).

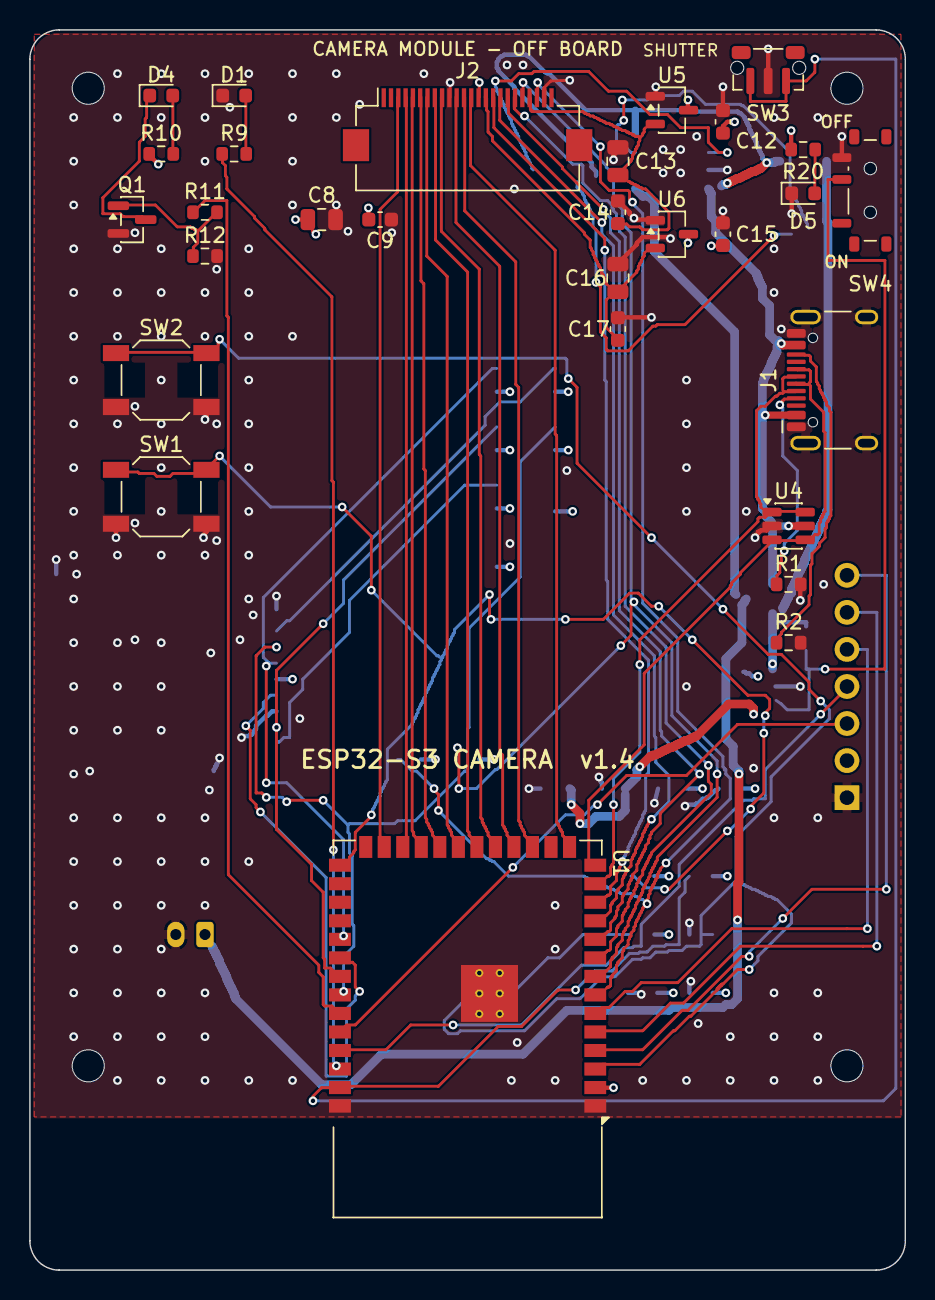
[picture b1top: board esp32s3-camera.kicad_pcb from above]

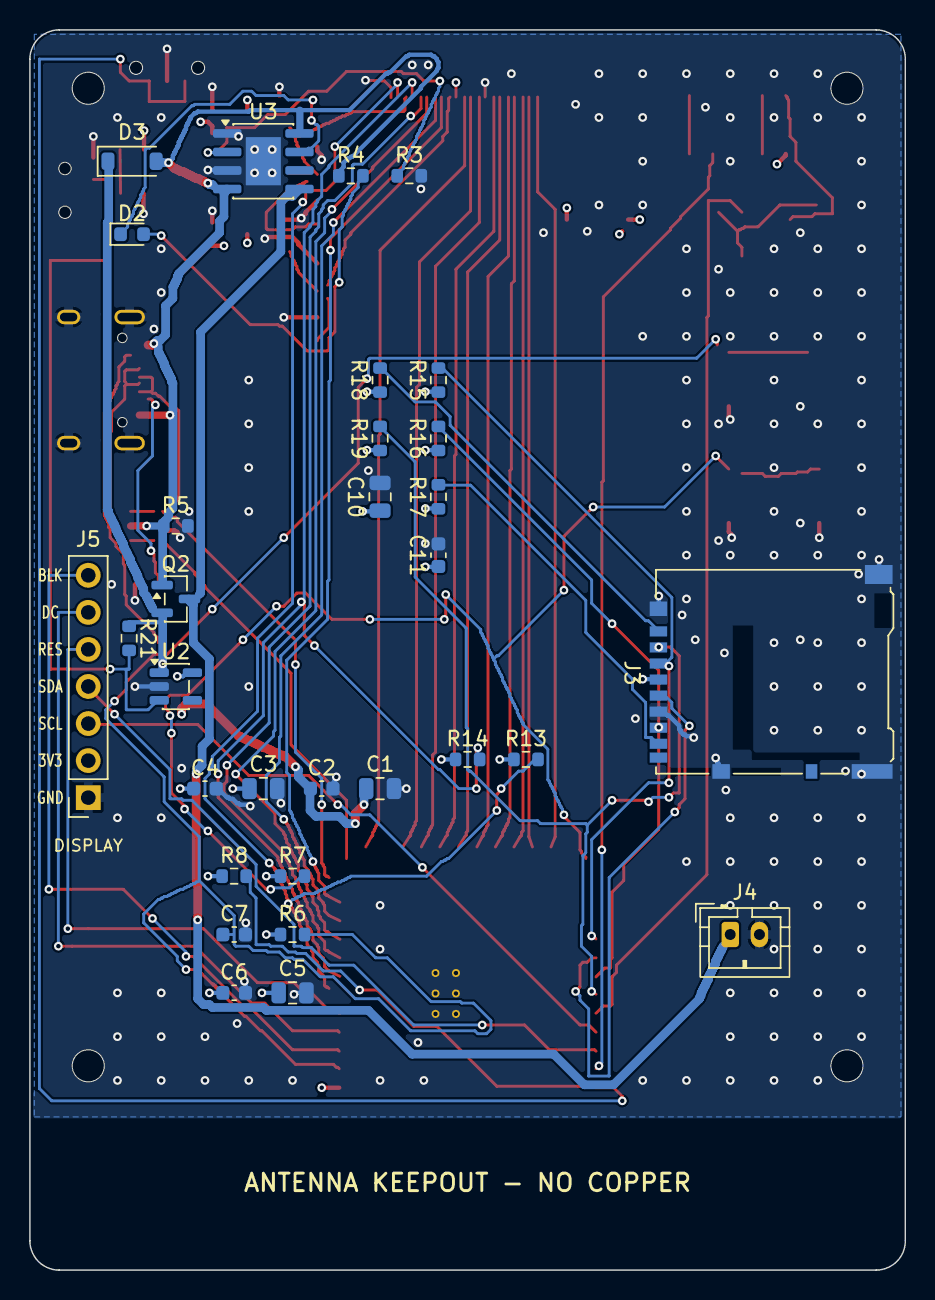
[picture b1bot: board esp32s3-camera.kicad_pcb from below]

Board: 4 copper layers, 60.0 x 85.0 mm, 64 parts (31 on the bottom side), 52 nets.

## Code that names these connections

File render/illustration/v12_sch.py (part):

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power LED D5 + R20. Text-level edit of esp32s3-camera.kicad_sch.

Steps
 1. U2 pin 3 (EN): rename the global label at its wire end from VSYS to LDO_EN.
 2. Add lib symbol Switch:SW_SPDT (copied from KiCad's Switch.kicad_sym).
 3. Add SW4, R21, R20, D5 with wires + global labels in a free area.
 4. Title block rev -> 1.2.
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assert "(rev \"1.1\")" in text, "expected v1.1 schematic"

# ---------------------------------------------------------------- 1. relabel U2 EN
# wire from U2 pin 3 (162.56,299.72) ends at (160.02,299.72); the VSYS global label sits there
m = re.search(r'\(global_label "VSYS"\s*\(shape [a-z_]+\)\s*\(at 160\.02 299\.72 [\d.]+\)', text)
assert m, "VSYS label at U2 pin 3 not found"
text = text[:m.start()] + m.group(0).replace('"VSYS"', '"LDO_EN"') + text[m.end():]
print("U2 pin 3 label -> LDO_EN")

# ---------------------------------------------------------------- 2. lib symbol SW_SPDT
lib_text = LIB.read_text(encoding="utf-8")
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p3 = sheet_pt(X0, y, 0, *sw_pins["3"])
# common -> LDO_EN (wire to the left)
lx = p2[0] - 2.54
new += wire(p2[0], p2[1], lx, p2[1]) + glabel("LDO_EN", lx, p2[1], 180)
# pin 3 -> GND (wire to the right)
rx = p3[0] + 2.54
new += wire(p3[0], p3[1], rx, p3[1]) + glabel("GND", rx, p3[1], 0)
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new += symbol("Device:R", "R21", "100k", "Resistor_SMD:R_0603_1608Metric", "C25803", X0, y, 0, ["1", "2"], ids["R21"])
a = sheet_pt(X0, y, 0, *R_PINS["1"]); b = sheet_pt(X0, y, 0, *R_PINS["2"])
top, bot = (a, b) if a[1] < b[1] else (b, a)
new += wire(top[0], top[1], top[0], top[1] - 2.54) + glabel("VSYS", top[0], top[1] - 2.54, 90)
new += wire(bot[0], bot[1], bot[0], bot[1] + 2.54) + glabel("LDO_EN", bot[0], bot[1] + 2.54, 270)

# R20 1k from +3V3 -----------------------------------------------------
y = 149.86
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a = sheet_pt(X0, y, 0, *R_PINS["1"]); b = sheet_pt(X0, y, 0, *R_PINS["2"])
top, bot = (a, b) if a[1] < b[1] else (b, a)
new += wire(top[0], top[1], top[0], top[1] - 2.54) + glabel("+3V3", top[0], top[1] - 2.54, 90)
new += wire(bot[0], bot[1], bot[0], bot[1] + 2.54) + glabel("LEDA_PWR", bot[0], bot[1] + 2.54, 270)

# D5 blue power LED ----------------------------------------------------
y = 175.26
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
